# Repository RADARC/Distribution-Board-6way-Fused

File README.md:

# Distribution-Board-6way-Fused
clone of Distribution-Board-6way with fuses in mind

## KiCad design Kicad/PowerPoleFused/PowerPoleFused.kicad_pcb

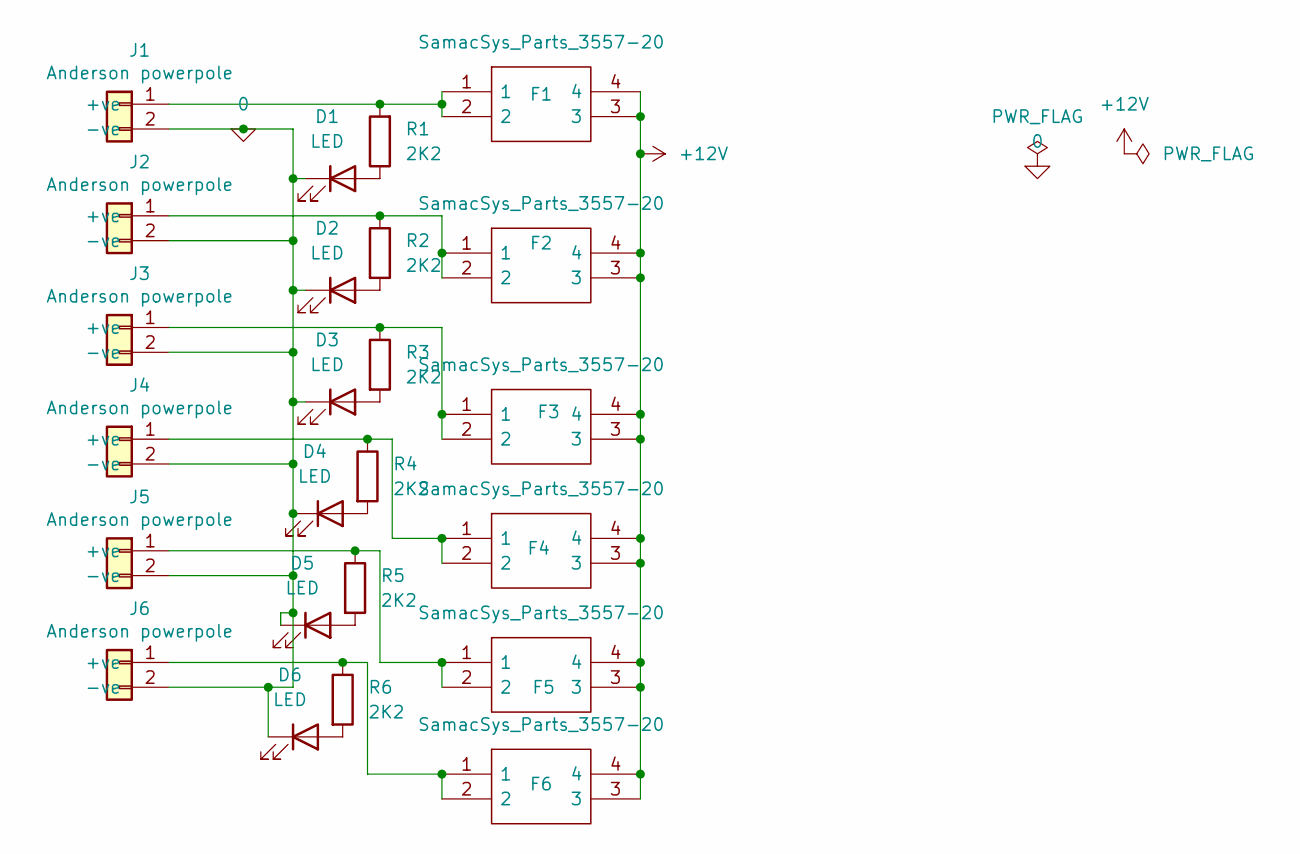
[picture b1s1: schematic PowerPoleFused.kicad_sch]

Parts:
D1, D2, D3, D4, D5, D6: LED; LED_D5.0mm
F1, F2, F3, F4, F5, F6: SamacSys_Parts_3557-20; 355720; Mouser Part Number 534-3557-20
J1, J2, J3, J4, J5, J6: Anderson powerpole; Anderson_powerpole_2w
R1, R2, R3, R4, R5, R6: 2K2; R_Axial_DIN0207_L6.3mm_D2.5mm_P7.62mm_Horizontal

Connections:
0: D1.1 (K), D2.1 (K), D3.1 (K), D4.1 (K), D5.1 (K), D6.1 (K), J1.2 (-ve), J2.2 (-ve), J3.2 (-ve), J4.2 (-ve), J5.2 (-ve), J6.2 (-ve)
+12V: F1.3, F1.4, F2.3, F2.4, F3.3, F3.4, F4.3, F4.4, F5.3, F5.4, F6.3, F6.4
unnamed: D1.2 (A), R1.1
unnamed: D2.2 (A), R2.2
unnamed: D3.2 (A), R3.2
unnamed: D4.2 (A), R4.2
unnamed: D5.2 (A), R5.2
unnamed: D6.2 (A), R6.2
unnamed: F1.1, F1.2, J1.1 (+ve), R1.2
unnamed: F2.1, F2.2, J2.1 (+ve), R2.1
unnamed: F3.1, F3.2, J3.1 (+ve), R3.1
unnamed: F4.1, F4.2, J4.1 (+ve), R4.1
unnamed: F5.1, F5.2, J5.1 (+ve), R5.1
unnamed: F6.1, F6.2, J6.1 (+ve), R6.1

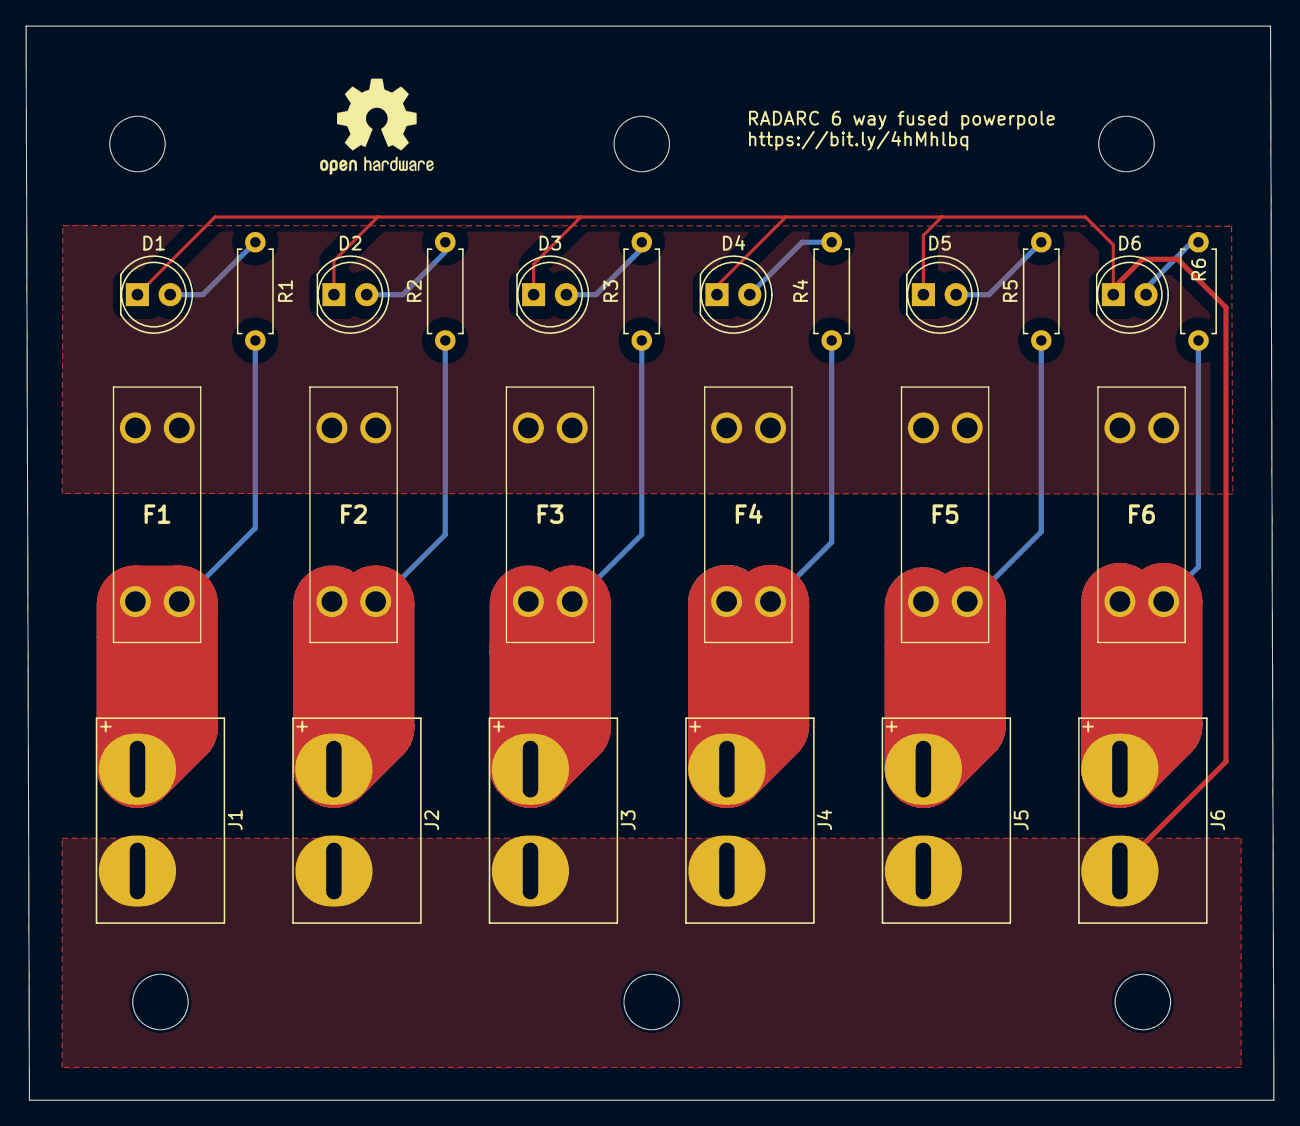
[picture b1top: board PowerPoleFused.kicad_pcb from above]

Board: 2 copper layers, 96.8 x 83.3 mm, 24 parts (0 on the bottom side), 14 nets.

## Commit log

2025-02-14 Imported powerpole
2025-02-14 Laid out board 1st attempt
2025-02-14 Better routing of +ve layer
2025-02-20 Alighment of items
